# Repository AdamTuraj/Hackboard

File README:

# Hackboard

This README will be updated towards the end of the project. The board will run on an STM32 processor, specifically the STM32L476RG. Here is the current feature list:

- Micro SD Card Slot
- 2 DAC’s
- More LEDs!
- Exposed pads for every pin
- (Almost) Every pin from the MCU available

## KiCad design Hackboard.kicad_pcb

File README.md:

# 

**Every hardware hacker needs a development board. So why not make your own overkill one?**

The Hackboard is a "one board fits (almost) all" development board with many useful features to ensure it works with all projects! Whether you need to drive a motor, listen through a microphone, play music on a speaker or use various peripherals, the Hackboard has you covered.

Running on Arduino or STM32CubeIDE, you can take full advantage of Hackboard due to its low learning curve. On top of all these features, it is super efficient and can easily run off a 9v battery for many hours. Still not interested. Get a larger overview of the features below!

Here's a deeper dive into the features:

- 80MHz Cortex M4 Core with 1 Mb of Flash and 128 Kb of SRAM
- Abilitiy to run on a 9v battery for around **150 HOURS**[^1]
- 45 GPIO pins
  - 2 SPI Interfaces[^2]
  - 1 I2C Interface
  - 1 CAN Interface
  - 1 UART Interface
  - 18 PWM Pins
  - 9 ADC's (Analog pins)
  - 2 DAC's
  - 1 OPAmp
- Arduino Uno Shield Compatible
- Same hole arrangement as Arduino UNO[^3]
- Extended header pads for easy probing
- Micro SD card slot
- PWM Addressable MOSFET capable of powering up to 54W
- 3 addressable LED's
- Barrel jack supporting up to 32V at 54W
- USB C port for flashing and power

[^1]: This assumes you are running with 0 peripherals connected, and are using a [Duracell 9v battery](https://www.duracell.com/wp-content/uploads/2016/03/MN1604_US_CT1.pdf)
[^2]: Only one may be used when an SD card is in use.
[^3]: The bottom right hole moved slightly up due to spacing issues.

## Assembly

> [!WARNING]
> This board CANNOT be assembled through JLCPCB due to many of the parts not being available at LCSC. Alternatives are using different PCB manufacturers or assembling it yourself

The BOM can be found in the production folder or the Digikey list [here](https://www.digikey.ca/en/mylists/list/BNXJM32ETT).

The extra MOSFET and related circuitry on pin 13 does not need to be soldered for the board to function (hence the DNP).

### Jumpers

JP1 and JP2 are jumpers that can be soldered/desoldered to achieve certain functionality.

JP1 must be bridged to enable the addressable LED's. JP2 must be left unbridged if the MOSFET is soldered.

### Work with Arduino

> [!NOTE]
> You must have an STLink to continue. They can be bought standalone or with a Nucleo board

A more detailed guide will be written up shortly. For now you may use [STM32Duino](https://github.com/stm32duino/Arduino_Core_STM32) to make it work with Arduino.

## Images

Schematic

All Layers

Top Layer (Signal / GND)

Second Layer (GND)

Third Layer (Power)

Bottom Layer (Signal / GND)

Bottom 3D View

## License

Hackboard is licensed under the GNU General Public License. See the full license text in [LICENSE](LICENSE).

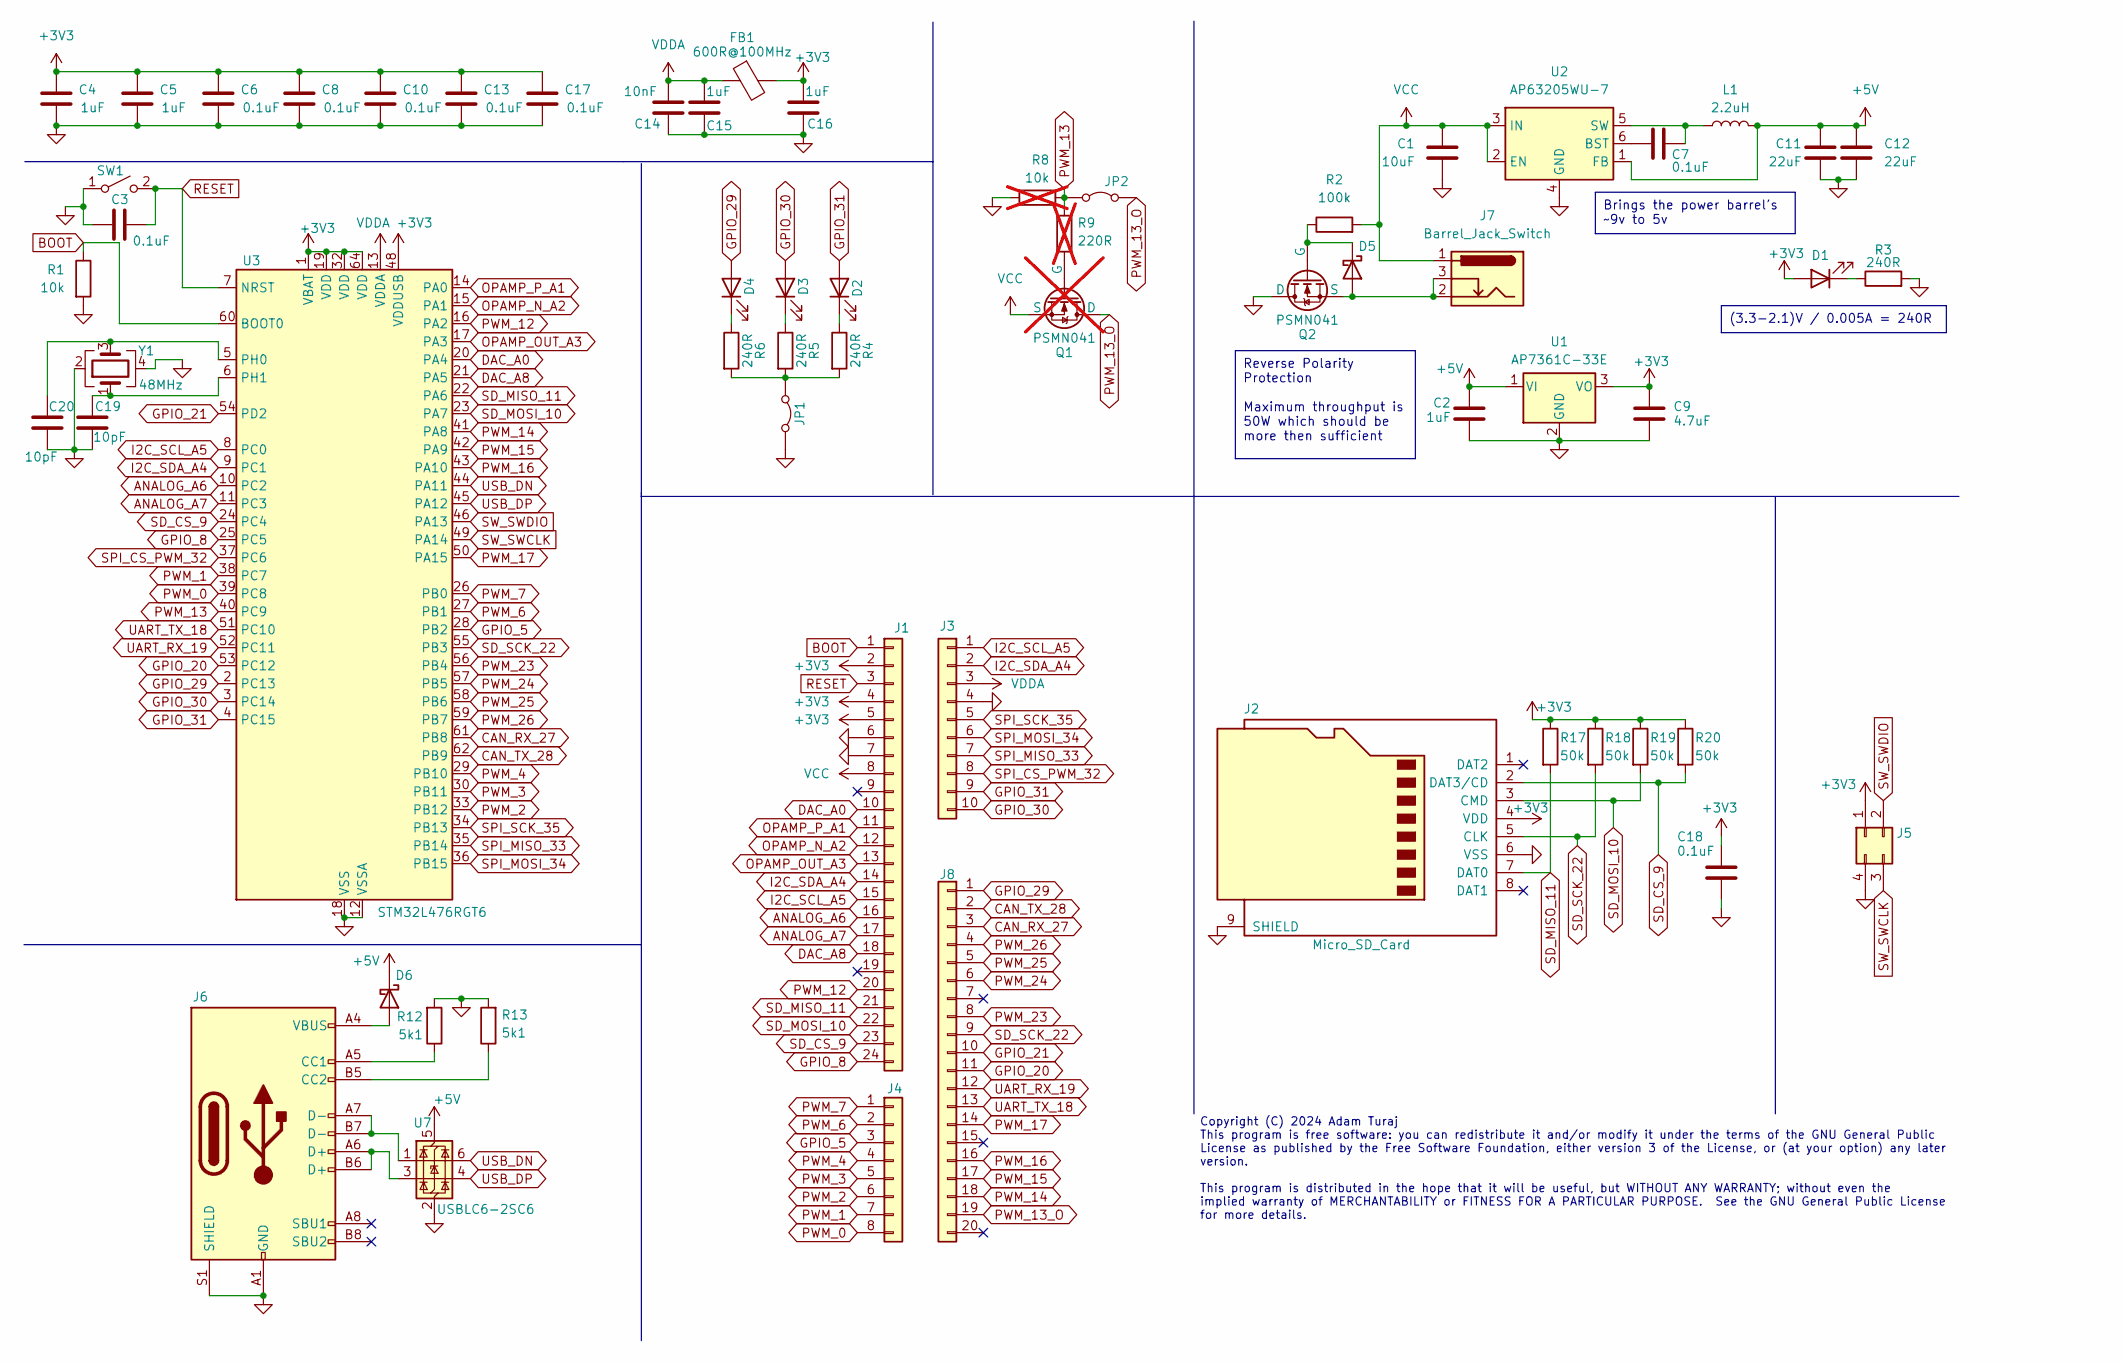
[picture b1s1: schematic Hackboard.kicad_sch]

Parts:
C1: 10uF; C_1206_3216Metric; MPN 0603DD106MAT2A
C2, C4, C5, C15, C16: 1uF; C_0603_1608Metric; MPN CC0603KRX7R7BB105
C3, C6, C7, C8, C10, C13, C17, C18: 0.1uF; C_0603_1608Metric; MPN GCM188R71H104KA57D
C9: 4.7uF; C_0603_1608Metric; MPN AP7361-33E-13
C11, C12: 22uF; C_0603_1608Metric; MPN C1608X5R1A226M080AC
C14: 10nF; C_0603_1608Metric; MPN 0603B103K500CT
C19, C20: 10pF; C_0603_1608Metric; MPN 0603N100J500CT
D1, D3: LED; LED_0603_1608Metric; MPN LTST-C190GKT
D2: LED; LED_0603_1608Metric; MPN LTST-C190TBKT
D4: LED; LED_0603_1608Metric; MPN LTST-C191KRKT
D5, D6: D_Schottky; D_SMB; MPN SSB44-E3/52T
FB1: 600R@100MHz; L_0603_1608Metric; MPN BLM18AG601SN1D
J1: Conn_01x24; PinSocket_1x24_P2.54mm_Vertical; MPN PPTC241LFBN-RC
J2: Micro_SD_Card; CONN9_MSD-1_CUD; MPN MSD-1-A
J3: Conn_01x10; PinSocket_1x10_P2.54mm_Vertical; MPN PPPC101LFBN-RC
J4: Conn_01x08; PinSocket_1x08_P2.54mm_Vertical; MPN 61300811821
J5: Conn_02x02_Counter_Clockwise; PinHeader_2x02_P2.54mm_Vertical
J6: USB_C_Receptacle_USB2.0_16P; USB_C_Receptacle_Amphenol_GSB1C4; MPN GSB1C411111DS1HR
J7: Barrel_Jack_Switch; CUI_PJ-002AH; MPN PJ-002AH
J8: Conn_01x20; PinSocket_1x20_P2.54mm_Vertical; MPN 61302011821
JP1, JP2: Jumper_2_Bridged; SolderJumper-2_P1.3mm_Open_RoundedPad1.0x1.5mm; MPN PPPC022LFBN-RC
L1: 2.2uH; L_Vishay_IFSC-1515AH_4x4x1.8mm; MPN IFSC1515AHER2R2M01
Q1: PSMN041; LFPAK56; MPN PSMN041-80YLX; not fitted
Q2: PSMN041; LFPAK56; MPN PSMN041-80YLX
R1: 10k; R_0603_1608Metric; MPN RMCF0603JT10K0
R2: 100k; R_0603_1608Metric; MPN ERJ-3EKF1003V
R3, R4, R5, R6: 240R; R_0603_1608Metric; MPN CRGCQ0603J220R
R8: 10k; R_0603_1608Metric; MPN RMCF0603JT10K0; not fitted
R9: 220R; R_0603_1608Metric; MPN CRGCQ0603J220R; not fitted
R12, R13: 5k1; R_0603_1608Metric; MPN RC0603FR-075K1L
R17, R18, R19, R20: 50k; R_0603_1608Metric; MPN RT0603BRD0750KL
SW1: SW_SPST; SW_SPST_PTS645; MPN PTS645SK43SMTR92 LFS
U1: AP7361C-33E; SOT-223-3_TabPin2; MPN AP7361C-33E-13
U2: AP63205WU-7; TSOT-23-6; MPN AP63205WU-7
U3: STM32L476RGT6; LQFP-64_10x10mm_P0.5mm; MPN STM32L476RGT6
U7: USBLC6-2SC6; SOT-23-6; MPN USBLC6-2SC6
Y1: 48MHz; Oscillator_SMD_Abracon_ASE-4Pin_3.2x2.5mm; MPN RH100-48.000-8-F-1015-EXT-TR

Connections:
+3V3: C4.1, C5.1, C6.1, C8.1, C9.2, C10.1, C13.1, C16.2, C17.1, C18.1, D1.2 (A), FB1.2, J1.2, J1.4, J1.5, J2.4 (VDD), J5.1, R17.1, R18.1, R19.1, R20.1, U1.3 (VO), U3.1 (VBAT), U3.19 (VDD), U3.32 (VDD), U3.48 (VDDUSB), U3.64 (VDD)
+5V: C2.1, C11.1, C12.1, D6.1 (K), L1.2, U1.1 (VI), U2.1 (FB), U7.5 (VBUS)
ANALOG_A6: J1.16, U3.10 (PC2)
ANALOG_A7: J1.17, U3.11 (PC3)
BOOT: J1.1, R1.1, U3.60 (BOOT0)
CAN_RX_27: J8.3, U3.61 (PB8)
CAN_TX_28: J8.2, U3.62 (PB9)
DAC_A0: J1.10, U3.20 (PA4)
DAC_A8: J1.18, U3.21 (PA5)
GND: C1.2, C2.2, C3.2, C4.2, C5.2, C6.2, C8.2, C9.1, C10.2, C11.2, C12.2, C13.2, C14.1, C15.1, C16.1, C17.2, C18.2, C19.2, C20.2, J1.6, J1.7, J2.6 (VSS), J2.9 (SHIELD), J3.4, J5.4, J6.A1 (GND), J6.A12 (GND), J6.B1 (GND), J6.B12 (GND), J6.S1 (SHIELD), JP1.1 (A), Q2.1 (D), R1.2, R3.2, R8.2, R12.2, R13.2, SW1.1 (A), U1.2 (GND), U2.4 (GND), U3.12 (VSSA), U3.18 (VSS), U3.31 (VSS), U3.47 (VSS), U3.63 (VSS), U7.2 (GND), Y1.2, Y1.4
GPIO_5: J4.3, U3.28 (PB2)
GPIO_8: J1.24, U3.25 (PC5)
GPIO_20: J8.11, U3.53 (PC12)
GPIO_21: J8.10, U3.54 (PD2)
GPIO_29: D4.2 (A), J8.1, U3.2 (PC13)
GPIO_30: D3.2 (A), J3.10, U3.3 (PC14)
GPIO_31: D2.2 (A), J3.9, U3.4 (PC15)
I2C_SCL_A5: J1.15, J3.1, U3.8 (PC0)
I2C_SDA_A4: J1.14, J3.2, U3.9 (PC1)
unnamed: D1.1 (K), R3.1
unnamed: D2.1 (K), R4.1
unnamed: D3.1 (K), R5.1
unnamed: D4.1 (K), R6.1
unnamed: D5.2 (A), J7.2, J7.3, Q2.3 (S)
unnamed: D5.1 (K), Q2.2 (G), R2.1
unnamed: D6.2 (A), J6.A4 (VBUS), J6.A9 (VBUS), J6.B4 (VBUS), J6.B9 (VBUS)
unnamed: J6.A5 (CC1), R12.1
unnamed: J6.B5 (CC2), R13.1
unnamed: J6.A6 (D+), J6.B6 (D+), U7.3 (I/O2)
unnamed: J6.A7 (D-), J6.B7 (D-), U7.1 (I/O1)
unnamed: JP1.2 (B), R4.2, R5.2, R6.2
unnamed: Q1.2 (G), R9.1
unnamed: C7.1, U2.6 (BST)
unnamed: C7.2, L1.1, U2.5 (SW)
unnamed: C20.1, U3.5 (PH0), Y1.3
unnamed: C19.1, U3.6 (PH1), Y1.1
OPAMP_N_A2: J1.12, U3.15 (PA1)
OPAMP_OUT_A3: J1.13, U3.17 (PA3)
OPAMP_P_A1: J1.11, U3.14 (PA0)
PWM_0: J4.8, U3.39 (PC8)
PWM_1: J4.7, U3.38 (PC7)
PWM_2: J4.6, U3.33 (PB12)
PWM_3: J4.5, U3.30 (PB11)
PWM_4: J4.4, U3.29 (PB10)
PWM_6: J4.2, U3.27 (PB1)
PWM_7: J4.1, U3.26 (PB0)
PWM_12: J1.20, U3.16 (PA2)
PWM_13: JP2.1 (A), R8.1, R9.2, U3.40 (PC9)
PWM_13_O: J8.19, JP2.2 (B), Q1.1 (D)
PWM_14: J8.18, U3.41 (PA8)
PWM_15: J8.17, U3.42 (PA9)
PWM_16: J8.16, U3.43 (PA10)
PWM_17: J8.14, U3.50 (PA15)
PWM_23: J8.8, U3.56 (PB4)
PWM_24: J8.6, U3.57 (PB5)
PWM_25: J8.5, U3.58 (PB6)
PWM_26: J8.4, U3.59 (PB7)
RESET: C3.1, J1.3, SW1.2 (B), U3.7 (NRST)
SD_CS_9: J1.23, J2.2 (DAT3/CD), R20.2, U3.24 (PC4)
SD_MISO_11: J1.21, J2.7 (DAT0), R17.2, U3.22 (PA6)
SD_MOSI_10: J1.22, J2.3 (CMD), R19.2, U3.23 (PA7)
SD_SCK_22: J2.5 (CLK), J8.9, R18.2, U3.55 (PB3)
SPI_CS_PWM_32: J3.8, U3.37 (PC6)
SPI_MISO_33: J3.7, U3.35 (PB14)
SPI_MOSI_34: J3.6, U3.36 (PB15)
SPI_SCK_35: J3.5, U3.34 (PB13)
SW_SWCLK: J5.3, U3.49 (PA14)
SW_SWDIO: J5.2, U3.46 (PA13)
UART_RX_19: J8.12, U3.52 (PC11)
UART_TX_18: J8.13, U3.51 (PC10)
USB_DN: U3.44 (PA11), U7.6 (I/O1)
USB_DP: U3.45 (PA12), U7.4 (I/O2)
VCC: C1.1, J1.8, J7.1, Q1.3 (S), R2.2, U2.2 (EN), U2.3 (IN)
VDDA: C14.2, C15.2, FB1.1, J3.3, U3.13 (VDDA)

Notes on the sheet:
Brings the power barrel's ~9v to 5v
Reverse Polarity Protection Maximum throughput is 50W which should be more then sufficient
(3.3-2.1)V / 0.005A = 240R
Copyright (C) 2024 Adam Turaj This program is free software: you can redistribute it and/or modify it under the terms of the GNU General Public License as published by the Free Software Foundation, either version 3 of the License, or (at your option) any later version. This program is distributed i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

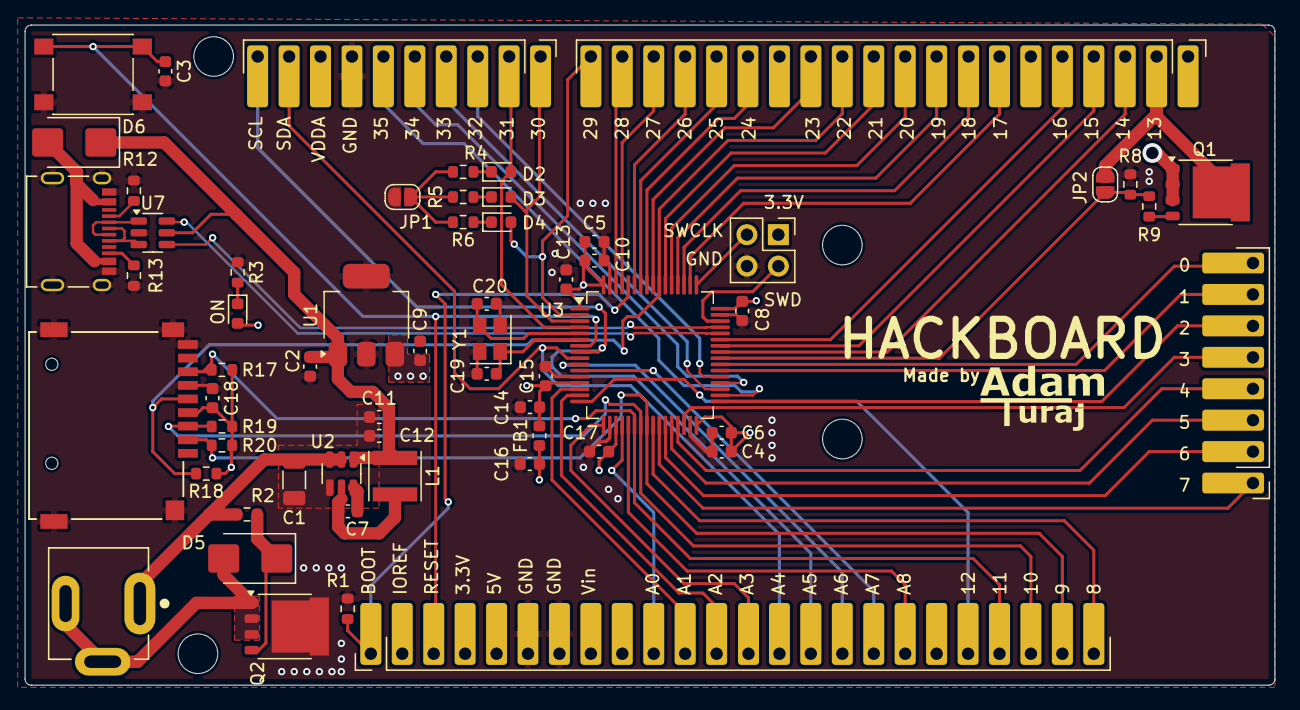
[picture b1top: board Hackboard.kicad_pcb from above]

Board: 4 copper layers, 101.0 x 53.3 mm, 64 parts (0 on the bottom side), 74 nets.

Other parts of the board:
H1, H2, H3, H4: MountingHole; MountingHole_3.2mm_M3

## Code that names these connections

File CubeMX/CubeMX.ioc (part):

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Mcu.Name=STM32L476R(C-E-G)Tx
Mcu.Package=LQFP64
Mcu.UserName=STM32L476RGTx
PA0.GPIOParameters=GPIO_Label
PA0.GPIO_Label=OPAMP_P_A1
PA0.Mode=PGA Connected
PA0.Signal=OPAMP1_VINP
PA1.GPIOParameters=GPIO_Label
PA1.GPIO_Label=OPAMP_N_A2
PA1.Mode=PGA Connected
PA1.Signal=OPAMP1_VINM
PA10.GPIOParameters=GPIO_Label
PA10.GPIO_Label=PWM_16
PA10.Signal=S_TIM1_CH3
PA11.GPIOParameters=GPIO_Label
PA11.GPIO_Label=USB_DM_17
PA11.Mode=Device_Only
PA11.Signal=USB_OTG_FS_DM
PA12.GPIOParameters=GPIO_Label
PA12.GPIO_Label=USB_DP_18
PA12.Mode=Device_Only
PA12.Signal=USB_OTG_FS_DP
PA13\ (JTMS-SWDIO).GPIOParameters=GPIO_Label
PA13\ (JTMS-SWDIO).GPIO_Label=SWDIO
PA13\ (JTMS-SWDIO).Mode=Serial_Wire
PA13\ (JTMS-SWDIO).Signal=SYS_JTMS-SWDIO
PA14\ (JTCK-SWCLK).GPIOParameters=GPIO_Label
PA14\ (JTCK-SWCLK).GPIO_Label=SWCLK
PA14\ (JTCK-SWCLK).Mode=Serial_Wire
PA14\ (JTCK-SWCLK).Signal=SYS_JTCK-SWCLK
PA15\ (JTDI).GPIOParameters=GPIO_Label
PA15\ (JTDI).GPIO_Label=PWM_19
PA15\ (JTDI).Signal=S_TIM2_CH1
PA2.GPIOParameters=GPIO_Label
PA2.GPIO_Label=PWM_12
PA2.Signal=S_TIM5_CH3
PA3.GPIOParameters=GPIO_Label
PA3.GPIO_Label=OPAMP_OUT_A3
PA3.Mode=PGA Connected
PA3.Signal=OPAMP1_VOUT
PA4.GPIOParameters=GPIO_Label
PA4.GPIO_Label=DAC_A0
PA4.Signal=COMP_DAC11_group
PA5.GPIOParameters=GPIO_Label
PA5.GPIO_Label=DAC_A8
PA5.Signal=COMP_DAC12_group
PA6.GPIOParameters=GPIO_Label
PA6.GPIO_Label=SD_MISO_11
PA6.Mode=Full_Duplex_Master
PA6.Signal=SPI1_MISO
PA7.GPIOParameters=GPIO_Label
PA7.GPIO_Label=SD_MOSI_10
PA7.Mode=Full_Duplex_Master
PA7.Signal=SPI1_MOSI
PA8.GPIOParameters=GPIO_Label
PA8.GPIO_Label=PWM_14
PA8.Signal=S_TIM1_CH1
PA9.GPIOParameters=GPIO_Label
PA9.GPIO_Label=PWM_13
PA9.Signal=S_TIM1_CH2
PB0.GPIOParameters=GPIO_Label
PB0.GPIO_Label=PWM_7
PB0.Signal=S_TIM3_CH3
PB1.GPIOParameters=GPIO_Label
PB1.GPIO_Label=PWM_6
PB1.Signal=S_TIM3_CH4
PB10.GPIOParameters=GPIO_Label
PB10.GPIO_Label=PWM_4
PB10.Signal=S_TIM2_CH3
PB11.GPIOParameters=GPIO_Label
PB11.GPIO_Label=PWM_3
PB11.Signal=S_TIM2_CH4
PB12.GPIOParameters=GPIO_Label
PB12.GPIO_Label=PWM_2
PB12.Signal=GPIO_Output
PB13.GPIOParameters=GPIO_Label
PB13.GPIO_Label=SPI_SCK_38
PB13.Mode=Full_Duplex_Master
PB13.Signal=SPI2_SCK
PB14.GPIOParameters=GPIO_Label
PB14.GPIO_Label=SPI_MISO_36
PB14.Mode=Full_Duplex_Master
PB14.Signal=SPI2_MISO
PB15.GPIOParameters=GPIO_Label
PB15.GPIO_Label=SPI_MOSI_37
PB15.Mode=Full_Duplex_Master
PB15.Signal=SPI2_MOSI
PB2.GPIOParameters=GPIO_Label
PB2.GPIO_Label=GPIO_5
PB2.Signal=GPIO_Output
PB3\ (JTDO-TRACESWO).GPIOParameters=GPIO_Label
PB3\ (JTDO-TRACESWO).GPIO_Label=SD_SCK_31
PB3\ (JTDO-TRACESWO).Mode=Full_Duplex_Master
PB3\ (JTDO-TRACESWO).Signal=SPI1_SCK
PB4\ (NJTRST).GPIOParameters=GPIO_Label
PB4\ (NJTRST).GPIO_Label=PWM_30
PB4\ (NJTRST).Signal=S_TIM3_CH1
PB5.GPIOParameters=GPIO_Label
PB5.GPIO_Label=PWM_29
PB5.Signal=S_TIM3_CH2
PB6.GPIOParameters=GPIO_Label
PB6.GPIO_Label=PWM_28
PB6.Signal=S_TIM4_CH1
PB7.GPIOParameters=GPIO_Label
PB7.GPIO_Label=PWM_27
PB7.Signal=S_TIM4_CH2
PB8.GPIOParameters=GPIO_Label
PB8.GPIO_Label=CAN_RX_26
PB8.Mode=CAN_Activate
PB8.Signal=CAN1_RX
PB9.GPIOParameters=GPIO_Label
PB9.GPIO_Label=CAM_TX_25
PB9.Mode=CAN_Activate
PB9.Signal=CAN1_TX
PC0.GPIOParameters=GPIO_Label
PC0.GPIO_Label=SCL_A5
PC0.Mode=I2C
PC0.Signal=I2C3_SCL
PC1.GPIOParameters=GPIO_Label
PC1.GPIO_Label=SDA_A4
PC1.Mode=I2C
PC1.Signal=I2C3_SDA
PC10.GPIOParameters=GPIO_Label
PC10.GPIO_Label=UART_TX_20
PC10.Mode=Asynchronous
PC10.Signal=UART4_TX
PC11.GPIOParameters=GPIO_Label
PC11.GPIO_Label=UART_RX_21
PC11.Mode=Asynchronous
PC11.Signal=UART4_RX
PC12.GPIOParameters=GPIO_Label
PC12.GPIO_Label=GPIO_22
PC12.Signal=GPIO_Output
PC13.GPIOParameters=GPIO_Label
PC13.GPIO_Label=GPIO_24
PC13.Signal=GPIO_Output
PC14-OSC32_IN\ (PC14).GPIOParameters=GPIO_Label
PC14-OSC32_IN\ (PC14).GPIO_Label=GPIO_32
PC14-OSC32_IN\ (PC14).Signal=GPIO_Output
PC15-OSC32_OUT\ (PC15).GPIOParameters=GPIO_Label
PC15-OSC32_OUT\ (PC15).GPIO_Label=GPIO_33
PC15-OSC32_OUT\ (PC15).Signal=GPIO_Output
PC2.GPIOParameters=GPIO_Label
PC2.GPIO_Label=A6
PC2.Signal=ADCx_IN3
PC3.GPIOParameters=GPIO_Label
PC3.GPIO_Label=A7
PC3.Signal=ADCx_IN4
PC4.GPIOParameters=GPIO_Label
PC4.GPIO_Label=SD_CS_9
PC4.Signal=GPIO_Output
PC5.GPIOParameters=GPIO_Label
PC5.GPIO_Label=GPIO_8
PC5.Signal=GPIO_Output
PC6.GPIOParameters=GPIO_Label
PC6.GPIO_Label=PWM_SPI_CS_35
PC6.Signal=S_TIM8_CH1
PC7.GPIOParameters=GPIO_Label
PC7.GPIO_Label=PWM_1
PC7.Signal=S_TIM8_CH2
PC8.GPIOParameters=GPIO_Label
PC8.GPIO_Label=PWM_0
PC8.Signal=S_TIM8_CH3
PC9.GPIOParameters=GPIO_Label
PC9.GPIO_Label=PWM_15
PC9.Signal=S_TIM8_CH4
PD2.GPIOParameters=GPIO_Label
PD2.GPIO_Label=GPIO_23
PD2.Signal=GPIO_Output
PH0-OSC_IN\ (PH0).Mode=HSE-External-Oscillator
PH0-OSC_IN\ (PH0).Signal=RCC_OSC_IN
PH1-OSC_OUT\ (PH1).Mode=HSE-External-Oscillator
PH1-OSC_OUT\ (PH1).Signal=RCC_OSC_OUT
RCC.HSE_VALUE=48000000
RCC.SYSCLKFreq_VALUE=80000000
RCC.SYSCLKSource=RCC_SYSCLKSOURCE_PLLCLK
board=custom

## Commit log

2024-08-01 First push
2024-08-01 Update README; Add power line and SPI for Micro SD
2024-08-01 Rename README
2024-08-01 Add USB, SD Card, LED's and other small things
2024-08-04 Make some power changes, add logic shifters
2024-08-04 Finish schematic
2024-08-06 Make changes to schematic and start adding footprints
2024-08-06 Finish footprints and place initial footprints on PCB editor
2024-08-06 Make basis of out line and start placing components
2024-08-07 Continue Laying down parts
2024-08-08 Start routing PCB
2024-08-08 Continue tracing
2024-08-08 Finish tracing MCU pins
2024-08-09 Route power
2024-08-09 Change USB C footprint, fix DRC errors, adjust silkscreen
2024-08-10 Finish PCB
2024-08-10 Change MCU Pinout
2024-08-11 Finish up updated schematic, start outlining border
2024-08-12 Finish board layout
2024-08-12 Adjust pinout
2024-08-13 Finish tracing most digital lines
2024-08-13 Finish tracing all pins, start tracing power
2024-08-13 Finish tracing power, add STEP files
2024-08-13 Change connector size, change USB port, add 3d models, add final touches
2024-08-13 Change out LDO, add JLC parts
2024-08-14 Add some JLC parts
2024-08-22 Add reverse polarity protection, remove logic shifters, make misc changes to schematic
2024-08-22 Finish making changes to schematic
2024-08-23 Make changes to header, align headers and holes, start tracing
2024-08-24 Adjust pinout, start tracing
2024-08-24 Continue routing
2024-08-24 Continue tracing, switch MOSFET's and diodes
2024-08-25 Finish tracing
2024-08-25 Fix footprint for HSE, add logo and updated schematic
2024-08-25 Make some changes to the README
2024-08-25 Add 3d view image
2024-08-25 Remove background on 3d view, add final README
2024-08-25 Change image path
2024-08-25 Add production files
2024-08-25 Fix format issue
2024-08-25 Rotate MCU and retrace
2024-08-26 Finish tracing, update 3d view, add punctuation & change wording in README
2024-08-26 Slight change to silkscreen, remove config file
2024-08-26 Change BOM
2024-08-26 Change digkey list link
2024-08-31 Add power consumption data
2024-09-01 Update schematic, add layer previews
2024-09-01 Move top layer to proper folder
2024-09-01 Move bottom 3d view
2024-09-01 Fix formatting
2024-09-01 Add schematic to images
2024-09-03 Fix Typo #1
